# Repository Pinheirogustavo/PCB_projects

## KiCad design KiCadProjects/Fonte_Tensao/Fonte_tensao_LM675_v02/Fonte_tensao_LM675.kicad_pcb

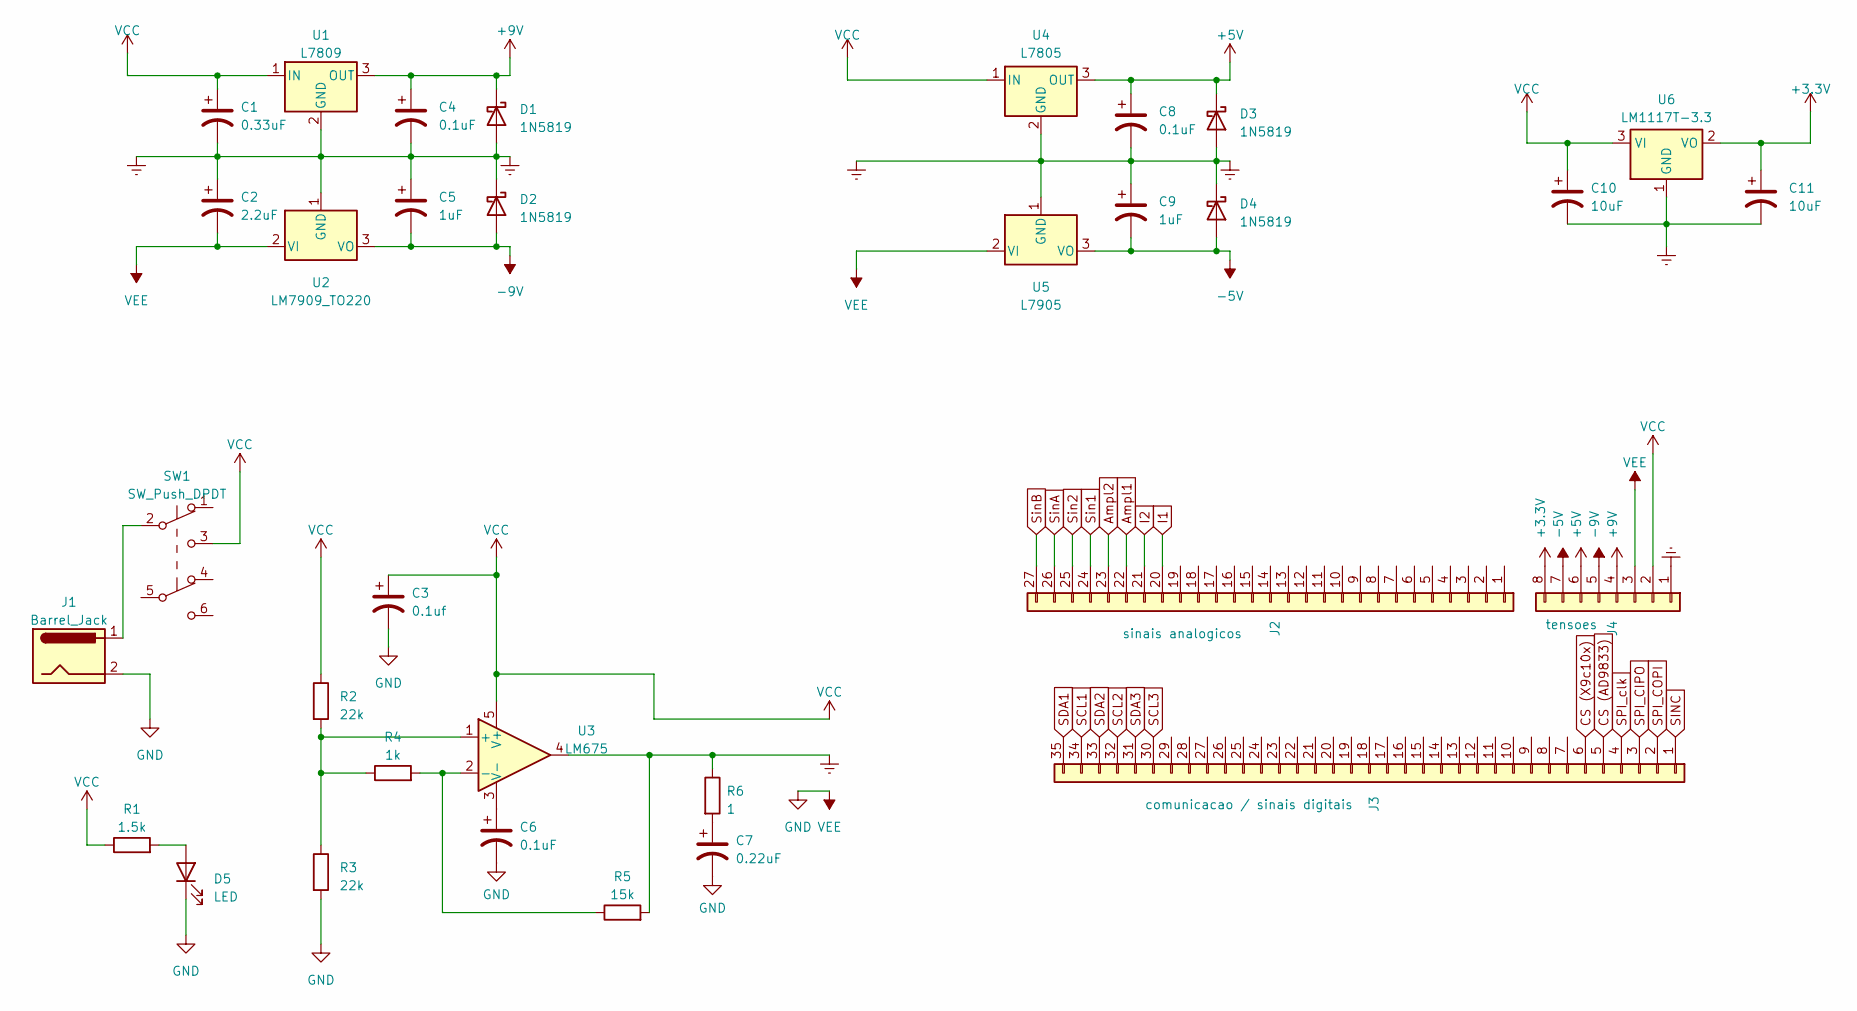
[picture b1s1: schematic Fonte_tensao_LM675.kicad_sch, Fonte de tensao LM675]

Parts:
C1: 0.33uF; CP_Radial_D5.0mm_P2.50mm
C2: 2.2uF; CP_Radial_D5.0mm_P2.50mm
C3: 0.1uf; CP_Radial_D5.0mm_P2.50mm
C4, C6, C8: 0.1uF; CP_Radial_D5.0mm_P2.50mm
C5, C9: 1uF; CP_Radial_D5.0mm_P2.50mm
C7: 0.22uF; CP_Radial_D5.0mm_P2.50mm
C10, C11: 10uF; CP_Radial_D5.0mm_P2.50mm
D1, D2, D3, D4: 1N5819; D_DO-41_SOD81_P10.16mm_Horizontal
D5: LED; LED_D5.0mm
J1: Barrel_Jack; BarrelJack_GCT_DCJ200-10-A_Horizontal
J2: sinais analogicos; PinHeader_1x27_P2.54mm_Vertical
J3: comunicacao / sinais digitais; PinHeader_1x35_P2.54mm_Vertical
J4: tensoes; PinHeader_1x08_P2.54mm_Vertical
R1: 1.5k; R_Axial_DIN0617_L17.0mm_D6.0mm_P20.32mm_Horizontal
R2, R3: 22k; R_Axial_DIN0617_L17.0mm_D6.0mm_P20.32mm_Horizontal
R4: 1k; R_Axial_DIN0617_L17.0mm_D6.0mm_P20.32mm_Horizontal
R5: 15k; R_Axial_DIN0617_L17.0mm_D6.0mm_P20.32mm_Horizontal
R6: 1; R_Axial_DIN0617_L17.0mm_D6.0mm_P20.32mm_Horizontal
SW1: SW_Push_DPDT; SW_PUSH_E-Switch_FS5700DP_DPDT
U1: L7809; TO-220-3_Vertical
U2: LM7909_TO220; TO-220-3_Vertical
U3: LM675; TO-220-5_P3.4x3.7mm_StaggerOdd_Lead3.8mm_Vertical
U4: L7805; TO-220-3_Vertical
U5: L7905; TO-220-3_Vertical
U6: LM1117T-3.3; TO-220-3_Vertical

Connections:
+3.3V: C11.1, J4.8, U6.2 (VO)
+5V: C8.1, D3.1 (K), J4.6, U4.3 (OUT)
+9V: C4.1, D1.1 (K), J4.4, U1.3 (OUT)
-5V: C9.2, D4.2 (A), J4.7, U5.3 (VO)
-9V: C5.2, D2.2 (A), J4.5, U2.3 (VO)
Ampl1: J2.22
Ampl2: J2.23
CS (AD9833): J3.5
CS (X9c10x): J3.6
Earth: C1.2, C2.1, C4.2, C5.1, C8.2, C9.1, C10.2, C11.2, D1.2 (A), D2.1 (K), D3.2 (A), D4.1 (K), J4.1, R5.2, R6.1, U1.2 (GND), U2.1 (GND), U3.4, U4.2 (GND), U5.1 (GND), U6.1 (GND)
GND: C2.2, C3.2, C6.2, C7.2, D5.1 (K), J1.2, J4.3, R3.2, U2.2 (VI), U5.2 (VI)
I1: J2.20
I2: J2.21
unnamed: C7.1, R6.2
unnamed: D5.2 (A), R1.2
unnamed: J1.1, SW1.2 (B)
unnamed: R2.2, R3.1, R4.1, U3.1 (+)
unnamed: R4.2, R5.1, U3.2 (-)
unnamed: C6.1, U3.3 (V-)
SCL1: J3.34
SCL2: J3.32
SCL3: J3.30
SDA1: J3.35
SDA2: J3.33
SDA3: J3.31
SINC: J3.1
SPI_CIPO: J3.3
SPI_COPI: J3.2
SPI_clk: J3.4
Sin1: J2.24
Sin2: J2.25
SinA: J2.26
SinB: J2.27
VCC: C1.1, C3.1, C10.1, J4.2, R1.1, R2.1, SW1.3 (C), U1.1 (IN), U3.5 (V+), U4.1 (IN), U6.3 (VI)

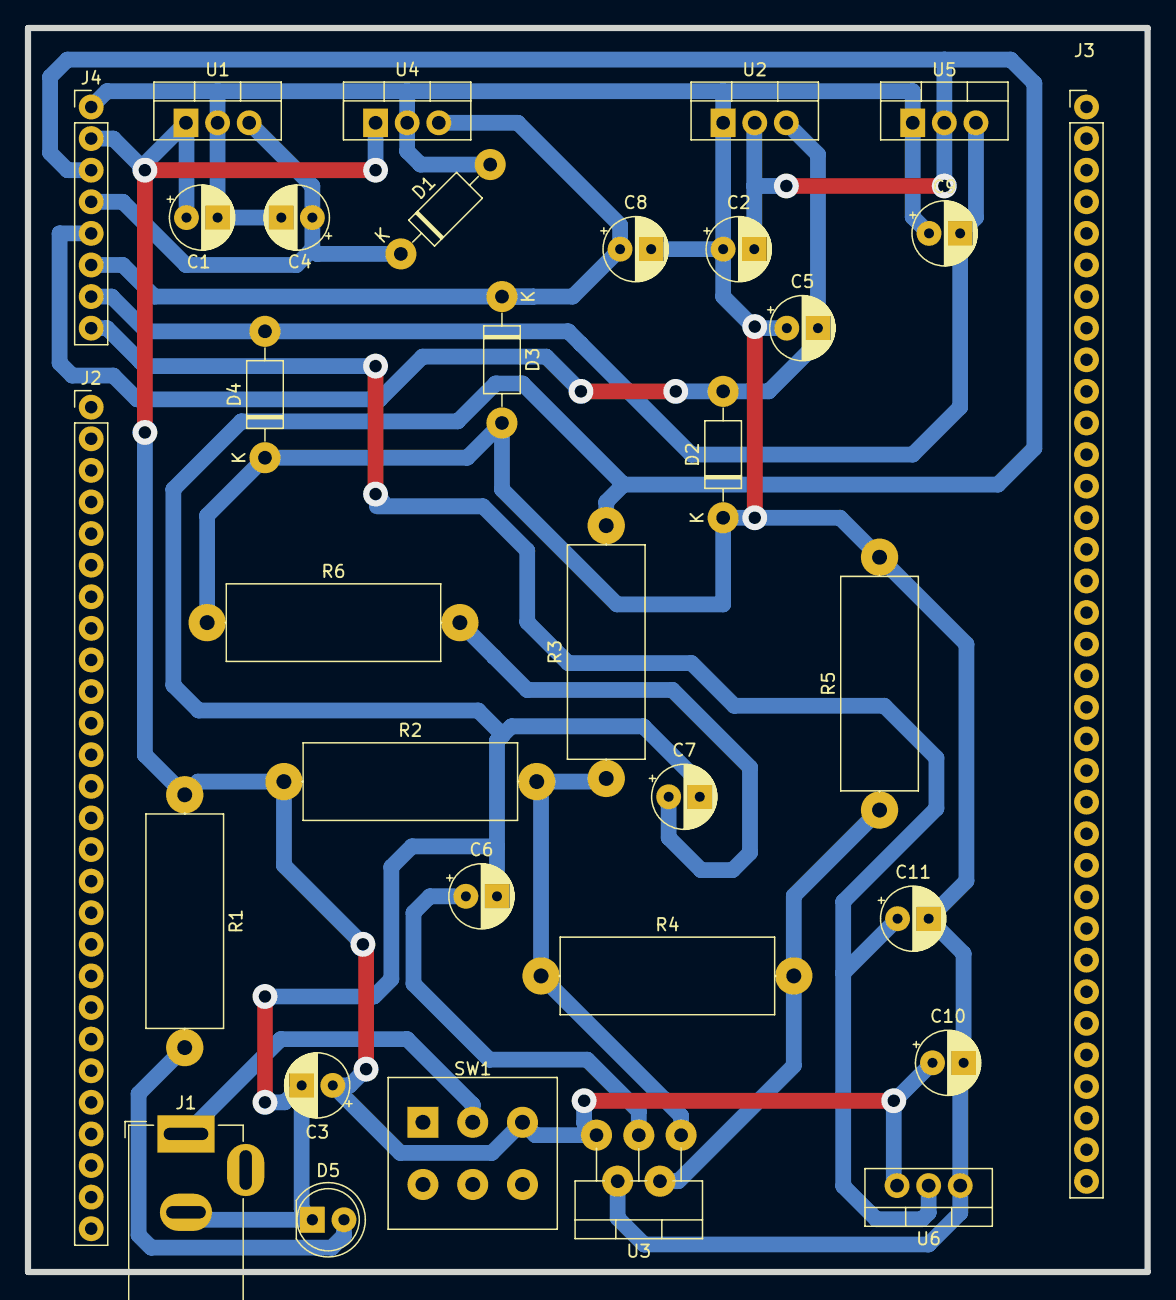
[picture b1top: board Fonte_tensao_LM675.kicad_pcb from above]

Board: 2 copper layers, 90.0 x 100.0 mm, 33 parts (0 on the bottom side), 14 nets.

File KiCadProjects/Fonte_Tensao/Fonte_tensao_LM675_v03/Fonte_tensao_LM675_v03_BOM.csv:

Id,Designador,Footprint,Quantidade,Designação,Fornecedor e referência
1,J1,BarrelJack_GCT_DCJ200-10-A_Horizontal,1,Barrel_Jack,
2,U3,TO-220-5_P3.4x3.7mm_StaggerOdd_Lead3.8mm_Vertical,1,LM675,
3,"C2,C7",CP_Radial_D5.0mm_P2.50mm,2,2.2uF,
4,"R1,R4",R_Axial_DIN0617_L17.0mm_D6.0mm_P20.32mm_Horizontal,2,1kΩ,
5,"D2,D4,D3,D1",D_DO-41_SOD81_P10.16mm_Horizontal,4,1N5819,
6,U1,TO-220-3_Vertical,1,L7809,
7,"C10,C11",CP_Radial_D5.0mm_P2.50mm,2,10uF,
8,J3,PinHeader_1x35_P2.54mm_Vertical,1,comunicacao / sinais digitais,
9,U6,TO-220-3_Vertical,1,LM1117T-3.3,
10,"C9,C5",CP_Radial_D5.0mm_P2.50mm,2,1uF,
11,R5,R_Axial_DIN0617_L17.0mm_D6.0mm_P20.32mm_Horizontal,1,15kΩ,
12,U2,TO-220-3_Vertical,1,LM7909_TO220,
13,"C8,C4",CP_Radial_D5.0mm_P2.50mm,2,0.1uF,
14,J4,PinHeader_1x08_P2.54mm_Vertical,1,tensoes,
15,J2,PinHeader_1x27_P2.54mm_Vertical,1,sinais analogicos,
16,"R2,R3",R_Axial_DIN0617_L17.0mm_D6.0mm_P20.32mm_Horizontal,2,22kΩ,
17,U4,TO-220-3_Vertical,1,L7805,
18,U5,TO-220-3_Vertical,1,L7905,
19,C1,CP_Radial_D5.0mm_P2.50mm,1,0.33uF,
20,R6,R_Axial_DIN0617_L17.0mm_D6.0mm_P20.32mm_Horizontal,1,1Ω,
21,D5,LED_D5.0mm,1,LED,
22,switch,chave gangorra kcd1,1,2 pinos,

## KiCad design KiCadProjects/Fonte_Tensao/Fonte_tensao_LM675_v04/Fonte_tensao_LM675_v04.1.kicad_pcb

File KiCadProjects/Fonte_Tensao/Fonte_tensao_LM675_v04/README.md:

# Fonte de tensão

## Especificidades da versão

A base do barramento é a  [versão 2 do barramento EITduino](https://github.com/Pinheirogustavo/PCB_projects/tree/main/KiCadProjects/Barramento_EITduino/V02)

LED vermelho: indica que uma fonte externa está conectada e acionada.

LED verde: indica o funcionamento do circuito de terra virtual.

Foram adicionados diversos pinos de terra AGND e DGND em relação às versões anteriores.

## Cuidados a serem tomados

## Esquemático

## PCB

## PCB-3D

## PCB Máscara

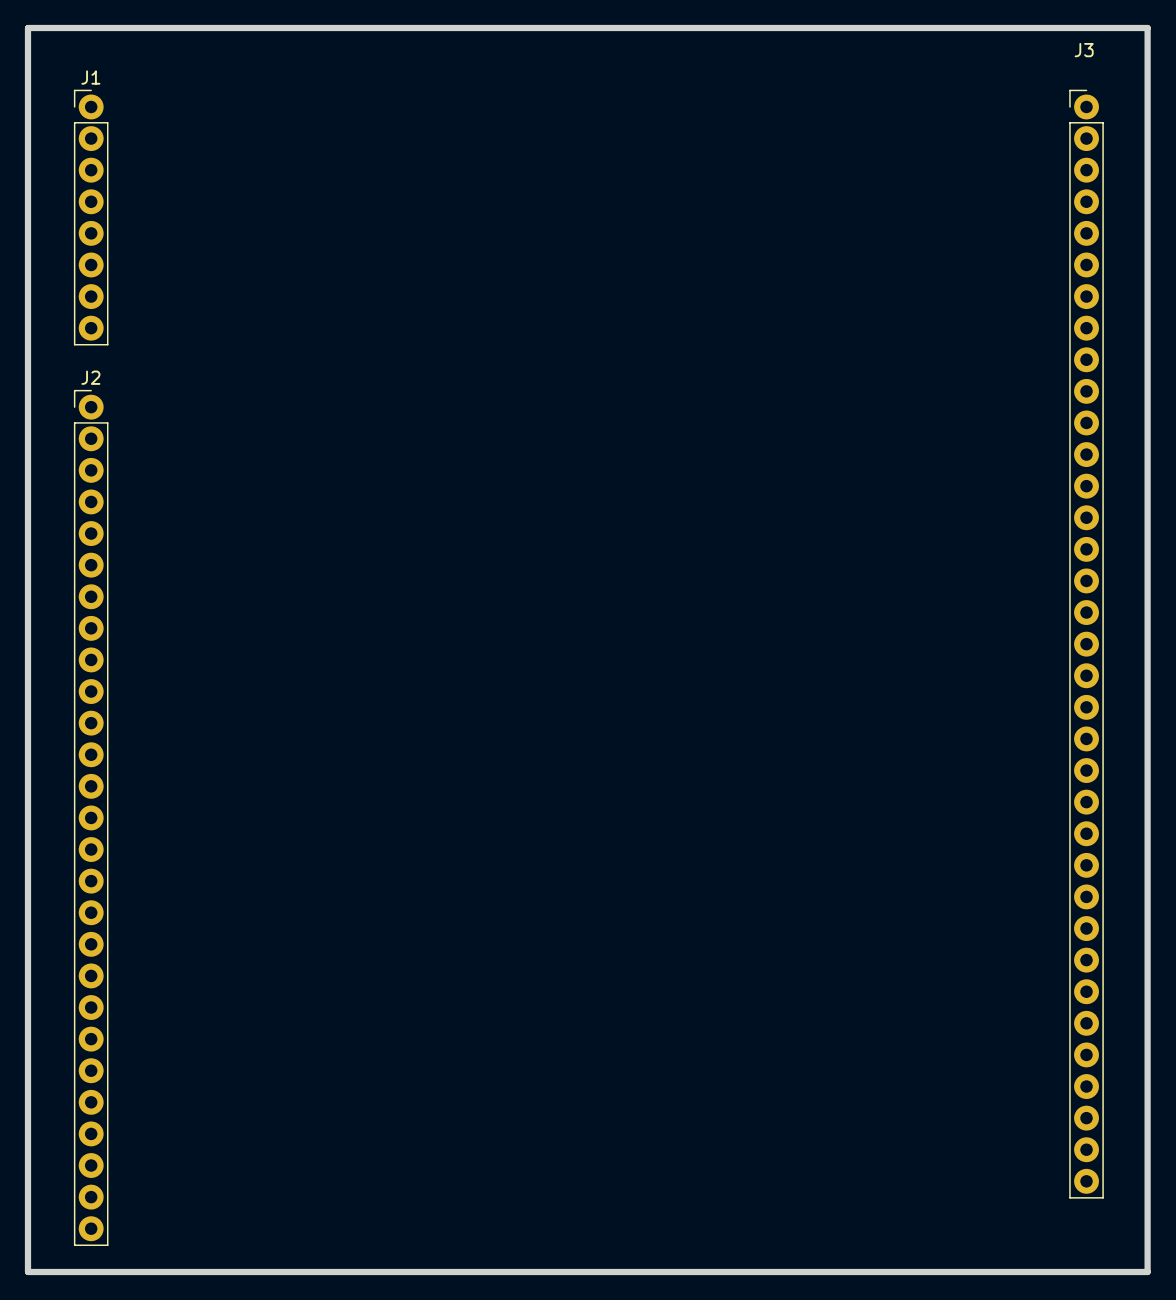
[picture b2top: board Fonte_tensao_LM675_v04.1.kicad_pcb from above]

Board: 2 copper layers, 90.0 x 100.0 mm, 3 parts (0 on the bottom side), 2 nets, no tracks yet.

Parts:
J1: alimentacao analogica; PinHeader_1x08_P2.54mm_Vertical
J2: sinais analogicos; PinHeader_1x27_P2.54mm_Vertical
J3: comunicacao / sinais digitais; PinHeader_1x35_P2.54mm_Vertical

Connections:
Earth: J1.1, J1.4, J1.6, J1.8, J2.14, J2.16, J2.18, J2.20, J2.22, J2.25, J3.2, J3.4, J3.6
GND: J3.14, J3.16, J3.18, J3.22, J3.25, J3.28, J3.31, J3.34

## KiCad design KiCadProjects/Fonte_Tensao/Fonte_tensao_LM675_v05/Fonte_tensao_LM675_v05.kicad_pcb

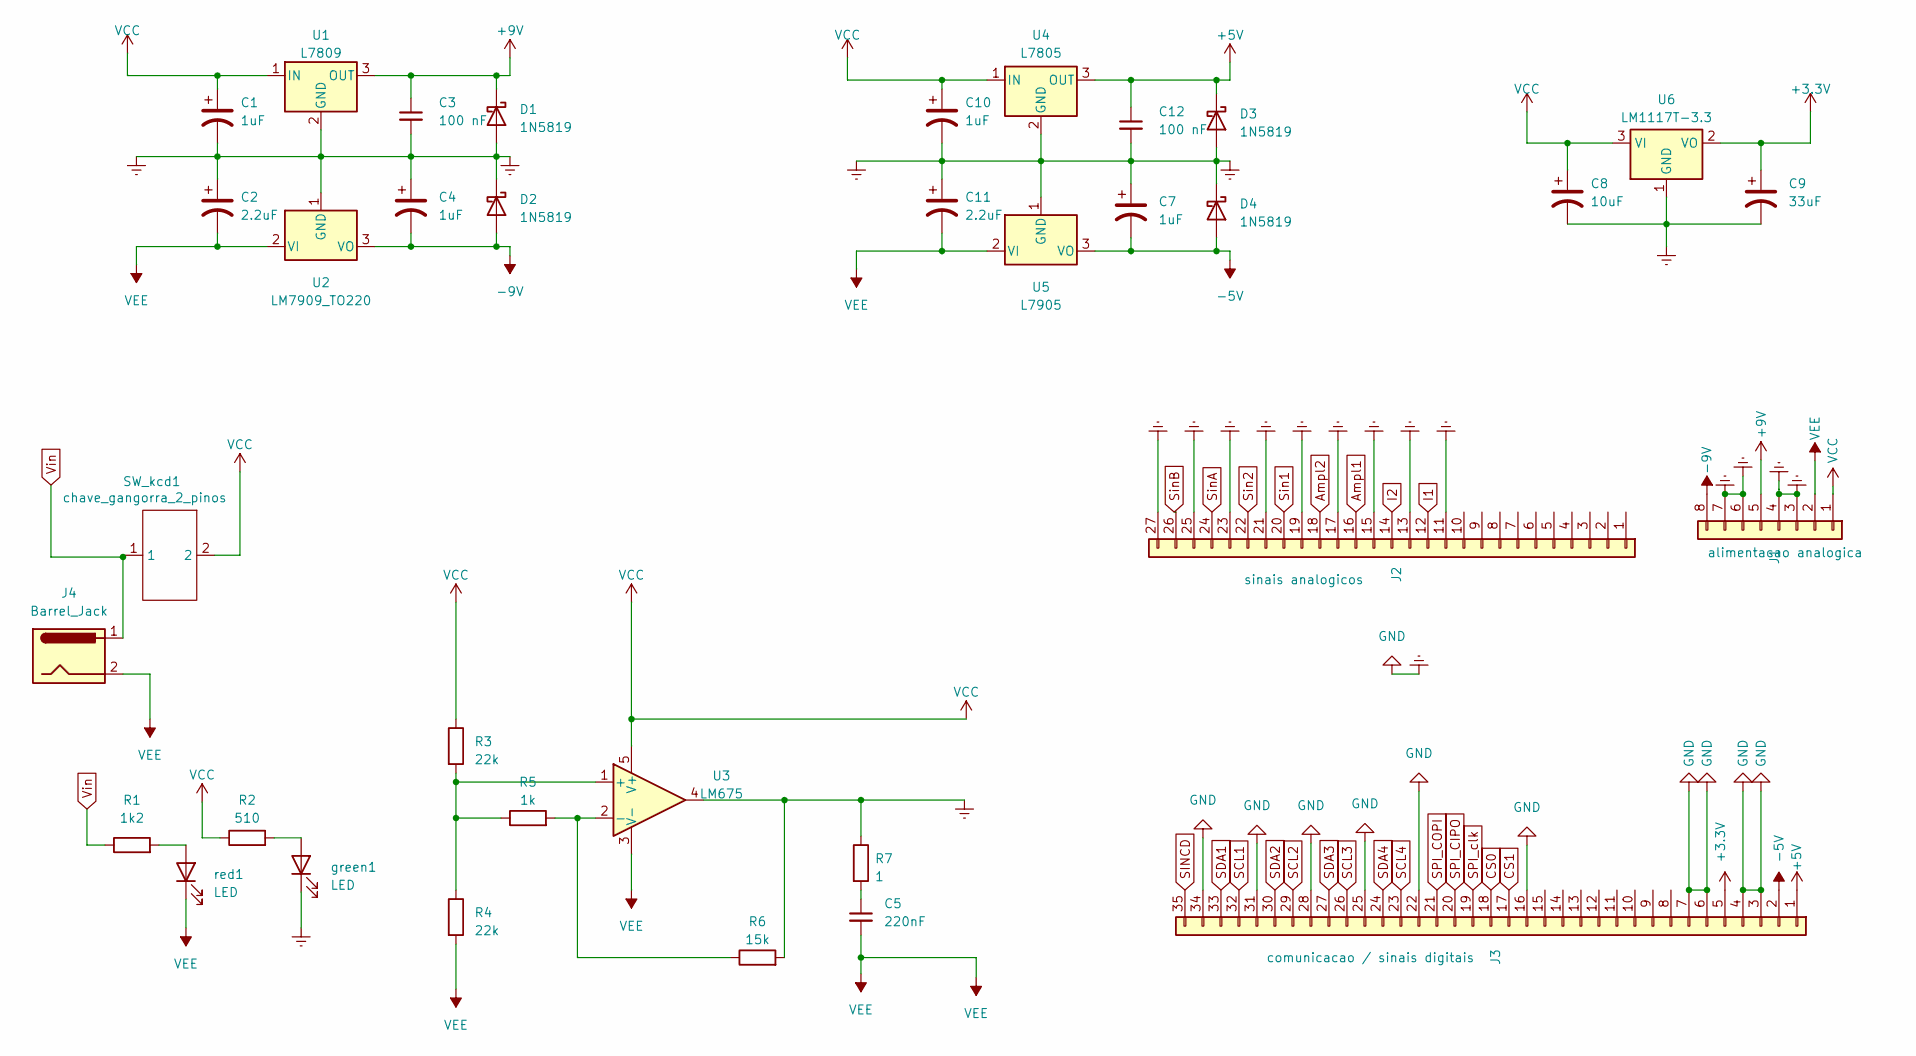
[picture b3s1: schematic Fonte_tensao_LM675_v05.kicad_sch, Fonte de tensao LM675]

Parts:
C1, C4, C7, C10: 1uF; CP_Radial_Tantal_D4.5mm_P2.50mm
C2, C11: 2.2uF; CP_Radial_Tantal_D4.5mm_P2.50mm
C3, C12: 100 nF; C_Disc_D3.0mm_W1.6mm_P2.50mm
C5: 220nF; C_Disc_D3.0mm_W1.6mm_P2.50mm
C8: 10uF; CP_Radial_Tantal_D4.5mm_P2.50mm
C9: 33uF; CP_Radial_Tantal_D4.5mm_P2.50mm
D1, D2, D3, D4: 1N5819; D_DO-41_SOD81_P10.16mm_Horizontal
J1: alimentacao analogica; PinHeader_1x08_P2.54mm_Vertical
J2: sinais analogicos; PinHeader_1x27_P2.54mm_Vertical
J3: comunicacao / sinais digitais; PinHeader_1x35_P2.54mm_Vertical
J4: Barrel_Jack; BarrelJack_GCT_DCJ200-10-A_Horizontal
R1: 1k2; R_Axial_DIN0207_L6.3mm_D2.5mm_P7.62mm_Horizontal
R2: 510; R_Axial_DIN0207_L6.3mm_D2.5mm_P7.62mm_Horizontal
R3, R4: 22k; R_Axial_DIN0207_L6.3mm_D2.5mm_P7.62mm_Horizontal
R5: 1k; R_Axial_DIN0207_L6.3mm_D2.5mm_P7.62mm_Horizontal
R6: 15k; R_Axial_DIN0207_L6.3mm_D2.5mm_P7.62mm_Horizontal
R7: 1; R_Axial_DIN0207_L6.3mm_D2.5mm_P7.62mm_Horizontal
SW_kcd1: chave_gangorra_2_pinos; chave gangorra 2 pinos
U1: L7809; TO-220-3_Vertical
U2: LM7909_TO220; TO-220-3_Vertical
U3: LM675; TO-220-5_P3.4x3.7mm_StaggerOdd_Lead3.8mm_Vertical
U4: L7805; TO-220-3_Vertical
U5: L7905; TO-220-3_Vertical
U6: LM1117T-3.3; TO-220-3_Vertical
green1: LED; LED_D5.0mm
red1: LED; LED_D5.0mm

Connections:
+3.3V: C9.1, J3.5, U6.2 (VO)
+5V: C12.1, D3.1 (K), J3.1, U4.3 (OUT)
+9V: C3.1, D1.1 (K), J1.5, U1.3 (OUT)
-5V: C7.2, D4.2 (A), J3.2, U5.3 (VO)
-9V: C4.2, D2.2 (A), J1.8, U2.3 (VO)
Ampl1: J2.16
Ampl2: J2.18
CS0: J3.18
CS1: J3.17
Earth: C1.2, C2.1, C3.2, C4.1, C7.1, C8.2, C9.2, C10.2, C11.1, C12.2, D1.2 (A), D2.1 (K), D3.2 (A), D4.1 (K), J1.3, J1.4, J1.6, J1.7, J2.11, J2.13, J2.15, J2.17, J2.19, J2.21, J2.23, J2.25, J2.27, J3.3, J3.4, J3.6, J3.7, J3.16, J3.22, J3.25, J3.28, J3.31, J3.34, R6.2, R7.1, U1.2 (GND), U2.1 (GND), U3.4, U4.2 (GND), U5.1 (GND), U6.1 (GND), green1.1 (K)
I1: J2.12
I2: J2.14
unnamed: C5.1, R7.2
unnamed: R3.2, R4.1, R5.1, U3.1 (+)
unnamed: R5.2, R6.1, U3.2 (-)
unnamed: R2.2, green1.2 (A)
unnamed: R1.2, red1.2 (A)
SCL1: J3.32
SCL2: J3.29
SCL3: J3.26
SCL4: J3.23
SDA1: J3.33
SDA2: J3.30
SDA3: J3.27
SDA4: J3.24
SINCD: J3.35
SPI_CIPO: J3.20
SPI_COPI: J3.21
SPI_clk: J3.19
Sin1: J2.20
Sin2: J2.22
SinA: J2.24
SinB: J2.26
VCC: C1.1, C8.1, C10.1, J1.1, R2.1, R3.1, SW_kcd1.2, U1.1 (IN), U3.5 (V+), U4.1 (IN), U6.3 (VI); also elsewhere on the board
VEE: C2.2, C5.2, C11.2, J1.2, J4.2, R4.2, U2.2 (VI), U3.3 (V-), U5.2 (VI), red1.1 (K); also elsewhere on the board
Vin: J4.1, R1.1, SW_kcd1.1; also elsewhere on the board

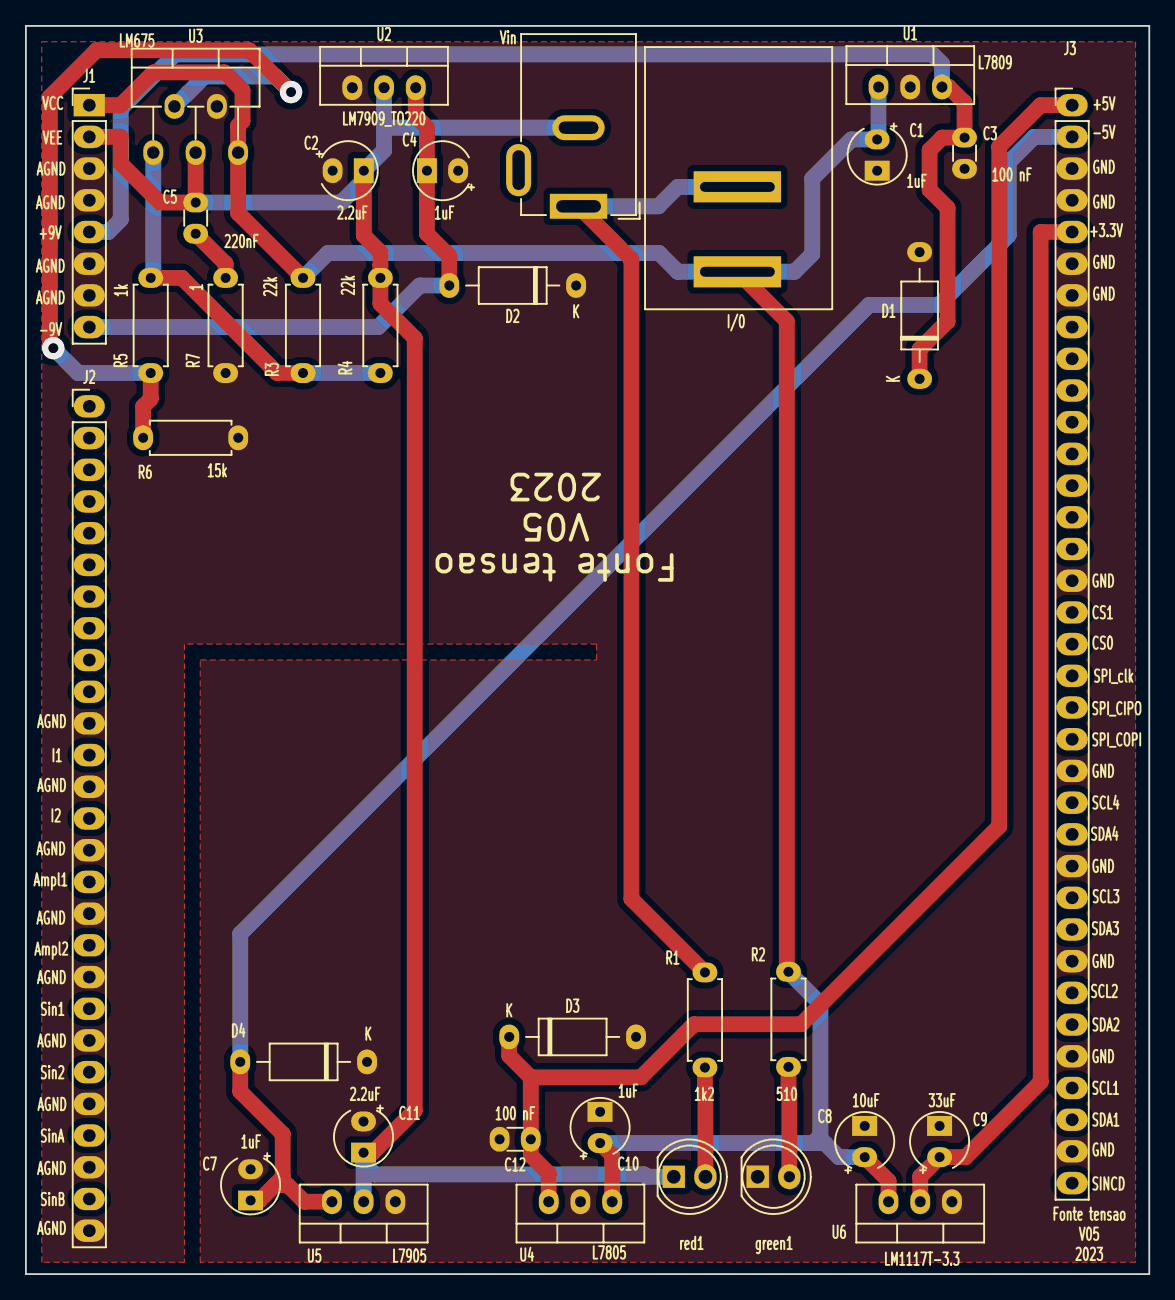
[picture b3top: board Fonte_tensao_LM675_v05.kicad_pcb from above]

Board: 2 copper layers, 90.0 x 100.0 mm, 35 parts (0 on the bottom side), 14 nets.

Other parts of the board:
I/0: Vin; chave gangorra 2 pinos
Vin: Vin; BarrelJack_GCT_DCJ200-10-A_Horizontal

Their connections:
VCC: I/0.2; also elsewhere on the board
VEE: Vin.2; also elsewhere on the board
Vin: I/0.1, Vin.1; also elsewhere on the board

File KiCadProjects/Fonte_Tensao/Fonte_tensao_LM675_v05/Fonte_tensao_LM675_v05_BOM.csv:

Id,Designador,Footprint,Quantidade,Designação,Fornecedor e referência,itens para 5 placas?
1,"D1,D4,D3,D2",D_DO-41_SOD81_P10.16mm_Horizontal,4,1N5819,,ok
2,C5,C_Disc_D3.0mm_W1.6mm_P2.50mm,1,220nF,,n
3,R7,R_Axial_DIN0207_L6.3mm_D2.5mm_P7.62mm_Horizontal,1,1,,Somente 10 ohms
4,U2,TO-220-3_Vertical,1,LM7909_TO220,,n
5,R5,R_Axial_DIN0207_L6.3mm_D2.5mm_P7.62mm_Horizontal,1,1k,,n
6,"C4,C1,C10,C7",CP_Radial_Tantal_D4.5mm_P2.50mm,4,1uF,,
7,C8,CP_Radial_Tantal_D4.5mm_P2.50mm,1,10uF,,
8,"R3,R4",R_Axial_DIN0207_L6.3mm_D2.5mm_P7.62mm_Horizontal,2,22k,,n
9,U3,TO-220-5_P3.4x3.7mm_StaggerOdd_Lead3.8mm_Vertical,1,LM675,,
10,I/0,chave gangorra 2 pinos,1,Vin,,
11,"green1,red1",LED_D5.0mm,2,LED,,
12,J3,PinHeader_1x35_P2.54mm_Vertical,1,comunicacao / sinais digitais,,
13,C9,CP_Radial_Tantal_D4.5mm_P2.50mm,1,33uF,,
14,"C11,C2",CP_Radial_Tantal_D4.5mm_P2.50mm,2,2.2uF,,
15,U5,TO-220-3_Vertical,1,L7905,,
16,J1,PinHeader_1x08_P2.54mm_Vertical,1,alimentacao analogica,,
17,J2,PinHeader_1x27_P2.54mm_Vertical,1,sinais analogicos,,
18,U6,TO-220-3_Vertical,1,LM1117T-3.3,,
19,"C3,C12",C_Disc_D3.0mm_W1.6mm_P2.50mm,2,100 nF,,
20,R2,R_Axial_DIN0207_L6.3mm_D2.5mm_P7.62mm_Horizontal,1,510,,n
21,R6,R_Axial_DIN0207_L6.3mm_D2.5mm_P7.62mm_Horizontal,1,15k,,n
22,U1,TO-220-3_Vertical,1,L7809,,
23,U4,TO-220-3_Vertical,1,L7805,,
24,Vin,BarrelJack_GCT_DCJ200-10-A_Horizontal,1,Vin,,
25,R1,R_Axial_DIN0207_L6.3mm_D2.5mm_P7.62mm_Horizontal,1,1k2,,n
